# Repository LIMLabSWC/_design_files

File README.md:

# _design_files

This repository stores the design files for all custom-made mechanical and electronic parts used in the lab.  
It is mirrored to the shared folder at:  
`/mnt/ceph/_design_files`

## Quick Start

- **Looking for a specific design?**
  - See the summary table below to find which folder contains the files you need.
  - Each major folder contains a README or index to help you navigate subfolders and file types.
- **Cloning the repository?**
  - Use `git clone --recurse-submodules` to get all submodules (see below for details).
- **Need to open a file?**
  - See folder READMEs for recommended software for each file type (e.g., Autodesk Inventor for `.ipt`, Eagle for `.sch`/`.brd`).

## Repository Structure Summary

| Folder                | Description                              | Main File Types      | Questions? Ask:          |
|-----------------------|------------------------------------------|----------------------|--------------------------|
| rat_behav_rig         | Rat behavioral rig CAD & docs            | .ipt, .stl, .pdf     | Viktor, Dammy, Lillianne |
| mouse-box             | Mouse behavioral box designs             | .ipt, .stl, .pdf     | Dammy, Quentin           |
| Repix_CAD_files       | Neuropixels implant design files         | .step, .stl          | Viktor, Elena            |
| np_calibration_files  | Neuropixels probe calibration data       | .csv                 | Viktor                   |
| Edmunds_designs       | Submodule: Edmund Chong's designs        | .ipt, .stl           | Edmund                   |

## Folder Structure

```
.
├── Edmunds_designs      # Submodule: Edmund Chong's mechanical designs
├── Repix_CAD_files      # Design files for Neuropixels implants     
├── mouse-box            # Design files for the mouse behavioral box
├── np_calibration_files # Neuropixels configuration files
├── rat_behav_rig        # Design files for the rat behavioral rig   
└── README.md
```

## External Design Repositories (Git Submodules)

Some folders in this repository are **Git submodules**—they link to external repositories maintained by individual lab members or collaborators.  
This structure allows each contributor to manage their own designs independently while keeping everything accessible in one place.

### Example: `Edmunds_designs`

- Maintained by: **Edmund Chong**
- Source repo: [edmundchong/Inventor](https://github.com/edmundchong/Inventor)
- Contains: Inventor files for various lab components

## About `.gitmodules`

The `.gitmodules` file tracks all submodules in this repository. It records the path and URL for each submodule, ensuring that everyone who clones the repository can initialize and update submodules easily.  
**Keep this file as long as you use submodules.** If you remove all submodules, you can safely delete `.gitmodules`.

## Cloning This Repository (with Submodules)

### Enabling Auto-Sync for Submodules (Git Hook)

To keep submodules like `Edmunds_designs` automatically in sync after pulling updates, this repository includes a Git hook stored in `.githooks/`.

After cloning, run:

```bash
./setup_hooks.sh
```

This configures Git to use the tracked hook, which:

- Automatically fetches and updates submodules after each `git pull`
- Commits and pushes the updated submodule pointer (if needed)

You only need to run this once per machine.

**Advanced:** You can customize or add your own hooks in the `.githooks/` directory if you want to automate other Git actions.

### Cloning with Submodules

To ensure you clone all linked submodules:

```bash
git clone --recurse-submodules https://github.com/akramilab/_design_files.git
```

If you've already cloned the repo without submodules:

```bash
git submodule update --init --recursive
```

### Keeping Submodules Up to Date Manually

To manually update a submodule (e.g., Edmund's):

```bash
cd Edmunds_designs
git pull origin main  # or the appropriate branch
cd ..
git add Edmunds_designs
git commit -m "Update Edmunds_designs submodule"
git push
```

Repeat for other submodules as needed.

### Notes

- Only maintainers of a submodule's source repo should make edits inside those folders.
- To contribute to a submodule, fork it or contact its maintainer.
- To **add a new submodule**, please contact the main repository maintainer.

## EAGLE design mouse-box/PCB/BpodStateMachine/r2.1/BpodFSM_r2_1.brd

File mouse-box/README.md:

# mouse-box

**Purpose:**
Design files for the mouse behavioral box, including mechanical parts, enclosures, PCBs, and accessories.

## Subfolders & Files

- `SP_box/` — CAD files for the single poke (SP) mouse box
- `PCB/` — Printed circuit board designs (modules, obsolete versions, etc.)
- `Nose Port/` — Nose port mechanical files
- `Head_fixation/` — Head fixation device designs (final and older versions)
- `Enclosure/` — Main enclosure CAD files
- `OldVersions/` — Archived/older versions of parts
- `Walls_schem.idw`, `Walls_schem.pdf` — Wall schematics (Inventor drawing and PDF)
- `Thumbs.db` — Windows thumbnail cache (can be ignored)

## File Types & Recommended Software

- `.ipt`, `.idw` — Autodesk Inventor (2021+ recommended)
- `.stl`, `.step`, `.stp` — 3D models (Inventor, Fusion 360, or free viewers)
- `.pdf` — Drawings, schematics, or documentation (any PDF reader)
- `.dxf`, `.dwg` — 2D CAD (AutoCAD, LibreCAD, or compatible)
- `.sch`, `.brd`, `.zip` (PCB) — Eagle or KiCad (for PCB design)
- `.db` — Windows system file (not needed for design work)

## How to Use

- Open CAD files with the recommended software above.
- See subfolder READMEs (if present) for part-specific instructions or assembly notes.
- For PCB work, see the `PCB/` folder and its submodules for details.
- For fabrication, check for `.pdf` or `.dxf` files for laser cutting or machining.

## Maintainer

- TBD (add name/email here)

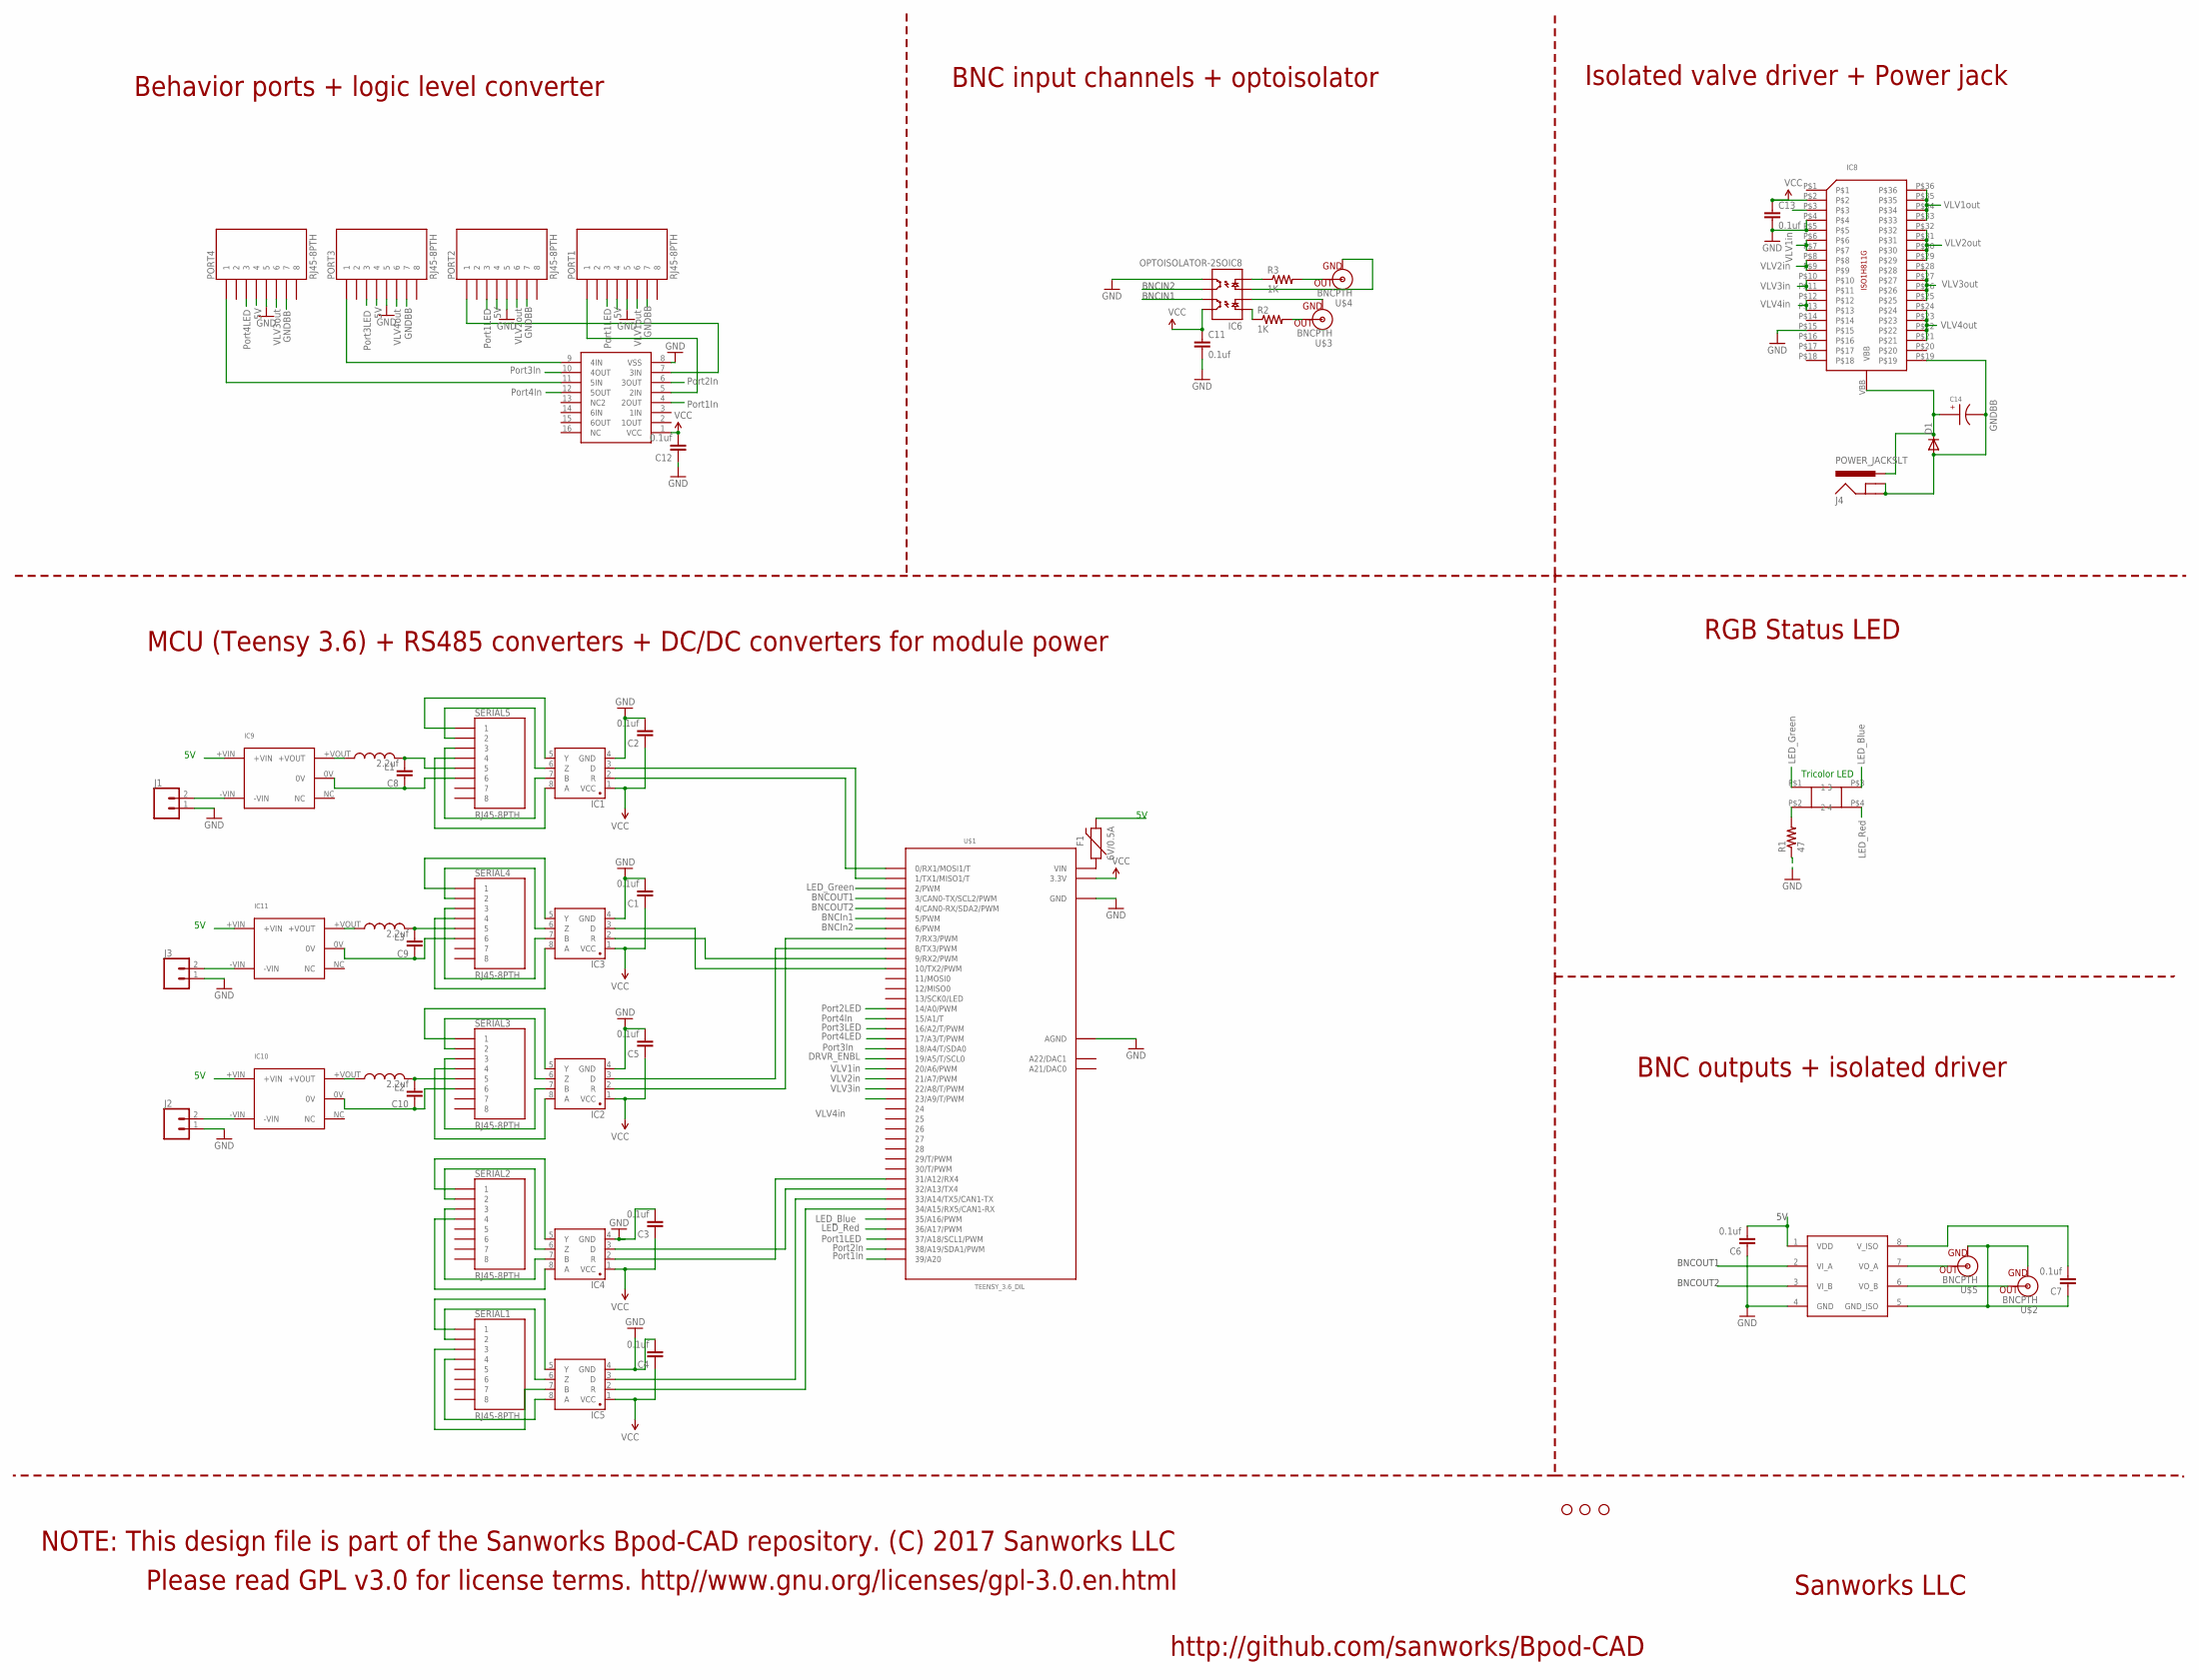
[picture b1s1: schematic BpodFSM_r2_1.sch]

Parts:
C1, C2, C3, C4, C5, C6, C7, C11, C12, C13: 0.1uf; 1206
C8, C9, C10: 2.2uf; 1206
C14: EEE-FK1H100UR
D1: DIODE-DO214AA; DO214AA
F1: 6V/0.5A; 1206
IC1, IC2, IC3, IC4, IC5: SN65HVD31DR; SO08
IC6: OPTOISOLATOR-2SOIC8; SO08-2
IC7: ADUM5240; SO08
IC8: ISO1H811G
IC9, IC10, IC11: MTU1D0505MC
IC12: CD4050; SO16
J1, J2, J3: CONN_02; 1X02
J4: POWER_JACKSLT; POWER_JACK_SLOT
JP3, JP4, JP5: STAND-OFF
L1, L2, L3: L-USL3225M; L3225M
PORT1, PORT2, PORT3, PORT4: RJ45-8PTH; RJ45-8
R1: 47; 1206
R2, R3: 1K; 1206
SERIAL1, SERIAL2, SERIAL3, SERIAL4, SERIAL5: RJ45-8PTH; RJ45-8
U$1: TEENSY_3.6_DIL
U$2, U$3, U$4, U$5: BNCPTH; BNC
U$8: SQUARE_TRICOLOR_LED

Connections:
5V: C6.2, F1.2, IC7.1 (VDD), IC9.+VIN, IC10.+VIN, IC11.+VIN, PORT1.4, PORT2.4, PORT3.4, PORT4.4
BNCIN1: IC6.7 (EM1), U$1.6 (6/PWM)
BNCIN2: IC6.6 (CL2), U$1.5 (5/PWM)
BNCOUT1: IC7.3 (VI_B), U$1.4 (4/CAN0-RX/SDA2/PWM)
BNCOUT2: IC7.2 (VI_A), U$1.3 (3/CAN0-TX/SCL2/PWM)
DRVR_ENBL: IC8.P$3, U$1.19/A5 (19/A5/T/SCL0)
GND: C1.2, C2.2, C3.2, C4.2, C5.2, C6.1, C11.2, C12.1, C13.2, IC1.4 (GND), IC2.4 (GND), IC3.4 (GND), IC4.4 (GND), IC5.4 (GND), IC6.5 (EM2), IC7.4 (GND), IC8.P$4, IC8.P$5, IC8.P$15, IC12.8 (VSS), J1.1, J2.1, J3.1, PORT1.5, PORT2.5, PORT3.5, PORT4.5, R1.1, U$1.AGND, U$1.GND, U$1.GND1 (GND)
GNDBB: C14.CATHODE, D1.A, IC8.P$19, J4.GND@1 (GNDBREAK), J4.GND@2 (GND), PORT1.7, PORT2.7, PORT3.7, PORT4.7
ISOGND: C7.1, IC7.5 (GND_ISO), U$2.GND, U$5.GND
LED_BLUE: U$1.35/A16 (35/A16/PWM), U$8.P$3 (3)
LED_GREEN: U$1.2 (2/PWM), U$8.P$1 (1)
LED_RED: U$1.36/A17 (36/A17/PWM), U$8.P$4 (4)
unnamed: IC3.8 (A), SERIAL4.4
unnamed: IC3.7 (B), SERIAL4.3
unnamed: IC3.6 (Z), SERIAL4.2
unnamed: IC3.5 (Y), SERIAL4.1
unnamed: IC3.2 (R), U$1.9 (9/RX2/PWM)
unnamed: IC3.3 (D), U$1.10 (10/TX2/PWM)
unnamed: IC1.8 (A), SERIAL5.4
unnamed: IC1.7 (B), SERIAL5.3
unnamed: IC1.6 (Z), SERIAL5.2
unnamed: IC1.5 (Y), SERIAL5.1
unnamed: IC1.2 (R), U$1.0 (0/RX1/MOSI1/T)
unnamed: IC1.3 (D), U$1.1 (1/TX1/MISO1/T)
unnamed: IC6.3 (A2), U$4.GND
unnamed: R3.2, U$4.S (OUT)
unnamed: R2.2, U$3.S (OUT)
unnamed: IC6.2 (C1), U$3.GND
unnamed: IC2.8 (A), SERIAL3.4
unnamed: IC2.7 (B), SERIAL3.3
unnamed: IC2.6 (Z), SERIAL3.2
unnamed: IC12.7 (3IN), PORT2.1
unnamed: IC2.5 (Y), SERIAL3.1
unnamed: IC2.2 (R), U$1.7 (7/RX3/PWM)
unnamed: C8.2, L1.2, SERIAL5.5
unnamed: IC12.9 (4IN), PORT3.1
unnamed: R1.2, U$8.P$2 (2)
unnamed: C8.1, IC9.0V, SERIAL5.6
unnamed: IC7.7 (VO_A), U$5.S (OUT)
unnamed: IC2.3 (D), U$1.8 (8/TX3/PWM)
unnamed: F1.1, U$1.VIN
unnamed: IC7.6 (VO_B), U$2.S (OUT)
unnamed: IC12.11 (5IN), PORT4.1
unnamed: IC5.8 (A), SERIAL1.4
unnamed: IC5.7 (B), SERIAL1.3
unnamed: IC5.6 (Z), SERIAL1.2
unnamed: IC5.5 (Y), SERIAL1.1
unnamed: IC4.8 (A), SERIAL2.4
unnamed: IC4.7 (B), SERIAL2.3
unnamed: IC4.6 (Z), SERIAL2.2
unnamed: IC9.+VOUT, L1.1
unnamed: IC4.5 (Y), SERIAL2.1
unnamed: IC9.-VIN, J1.2
unnamed: IC5.2 (R), U$1.34/A15 (34/A15/RX5/CAN1-RX)
unnamed: C10.1, IC10.0V, SERIAL3.6
unnamed: C10.2, L2.2, SERIAL3.5
unnamed: IC10.+VOUT, L2.1
unnamed: IC10.-VIN, J2.2
unnamed: C9.1, IC11.0V, SERIAL4.6
unnamed: IC5.3 (D), U$1.33/A14 (33/A14/TX5/CAN1-TX)
unnamed: C9.2, L3.2, SERIAL4.5
unnamed: IC11.+VOUT, L3.1
unnamed: IC11.-VIN, J3.2
unnamed: IC4.2 (R), U$1.31/A12 (31/A12/RX4)
unnamed: IC4.3 (D), U$1.32/A13 (32/A13/TX4)
unnamed: IC6.1 (A1), R2.1
unnamed: IC6.4 (C2), R3.1
unnamed: IC12.5 (2IN), PORT1.1
unnamed: C7.2, IC7.8 (V_ISO)
PORT1IN: IC12.4 (2OUT), U$1.39/A20
PORT1LED: PORT1.3, U$1.37/A18 (37/A18/SCL1/PWM)
PORT2IN: IC12.6 (3OUT), U$1.38/A19 (38/A19/SDA1/PWM)
PORT2LED: PORT2.3, U$1.14/A0 (14/A0/PWM)
PORT3IN: IC12.10 (4OUT), U$1.18/A4 (18/A4/T/SDA0)
PORT3LED: PORT3.3, U$1.16/A2 (16/A2/T/PWM)
PORT4IN: IC12.12 (5OUT), U$1.15/A1 (15/A1/T)
PORT4LED: PORT4.3, U$1.17/A3 (17/A3/T/PWM)
VBB: C14.ANODE, D1.C, IC8.VBB, J4.PWR
VCC: C1.1, C2.1, C3.1, C4.1, C5.1, C11.1, C12.2, C13.1, IC1.1 (VCC), IC2.1 (VCC), IC3.1 (VCC), IC4.1 (VCC), IC5.1 (VCC), IC6.8 (CL1), IC8.P$2, IC12.1 (VCC), U$1.3.3V, U$1.3.3V3 (3.3V)
VLV1IN: IC8.P$6, IC8.P$7, U$1.23/A9 (23/A9/T/PWM)
VLV1OUT: IC8.P$33, IC8.P$34, IC8.P$35, IC8.P$36, PORT1.6
VLV2IN: IC8.P$8, IC8.P$9, U$1.22/A8 (22/A8/T/PWM)
VLV2OUT: IC8.P$29, IC8.P$30, IC8.P$31, IC8.P$32, PORT2.6
VLV3IN: IC8.P$12, IC8.P$13, U$1.20/A6 (20/A6/PWM)
VLV3OUT: IC8.P$21, IC8.P$22, IC8.P$23, IC8.P$24, PORT3.6
VLV4IN: IC8.P$10, IC8.P$11, U$1.21/A7 (21/A7/PWM)
VLV4OUT: IC8.P$25, IC8.P$26, IC8.P$27, IC8.P$28, PORT4.6

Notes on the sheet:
Tricolor LED
LED_Blue
LED_Red
LED_Green
BNCIN1
BNCIN2
BNCIn1
BNCIn2
BNCOUT2
BNCOUT1
Port1In
Port2In
Port3In
Port4In
Port1LED
Port2LED
Port3LED
Port4LED
DRVR_ENBL
VLV2in
VLV3in
VLV4in
VLV1in
GNDBB
VLV1out
VLV2out
VLV3out
VLV4out
Sanworks LLC
http://github.com/sanworks/Bpod-CAD
Please read GPL v3.0 for license terms. http//www.gnu.org/licenses/gpl-3.0.en.html
NOTE: This design file is part of the Sanworks Bpod-CAD repository. (C) 2017 Sanworks LLC
Behavior ports + logic level converter
BNC input channels + optoisolator
Isolated valve driver + Power jack
RGB Status LED
BNC outputs + isolated driver
MCU (Teensy 3.6) + RS485 converters + DC/DC converters for module power

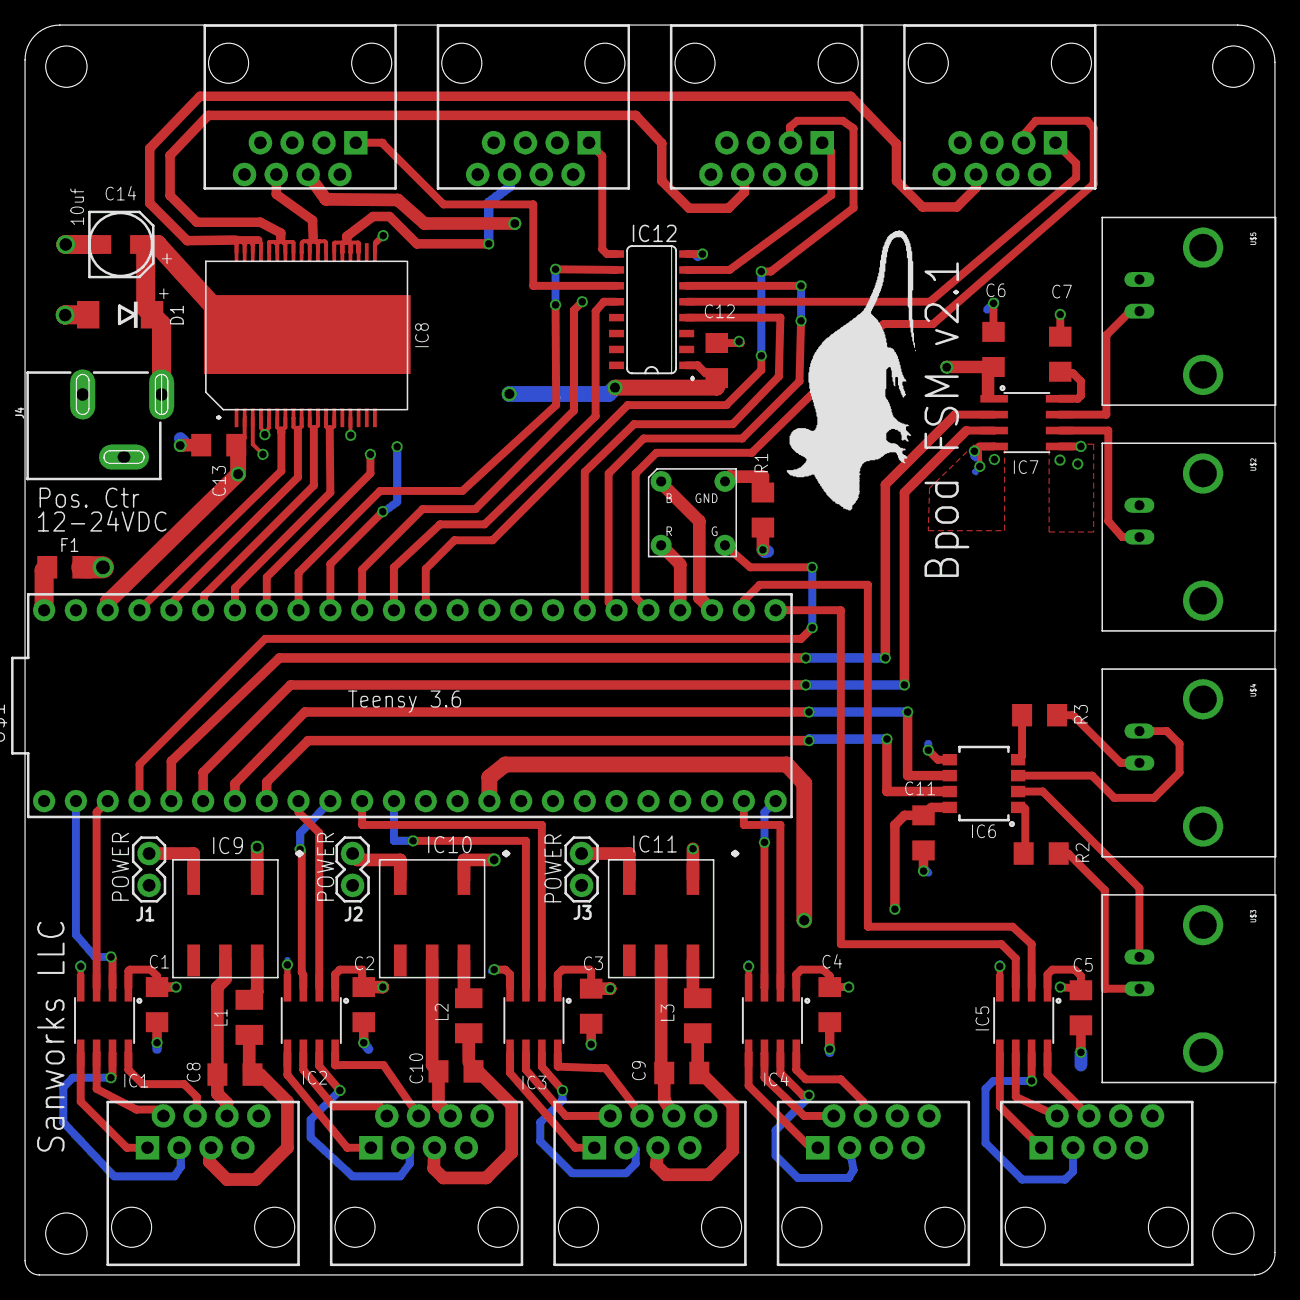
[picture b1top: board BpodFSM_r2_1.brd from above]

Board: 4 copper layers, 99.8 x 99.8 mm, 58 parts (0 on the bottom side), 87 nets.

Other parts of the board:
JP1: STAND-OFF
U$9: MOUSELOGO

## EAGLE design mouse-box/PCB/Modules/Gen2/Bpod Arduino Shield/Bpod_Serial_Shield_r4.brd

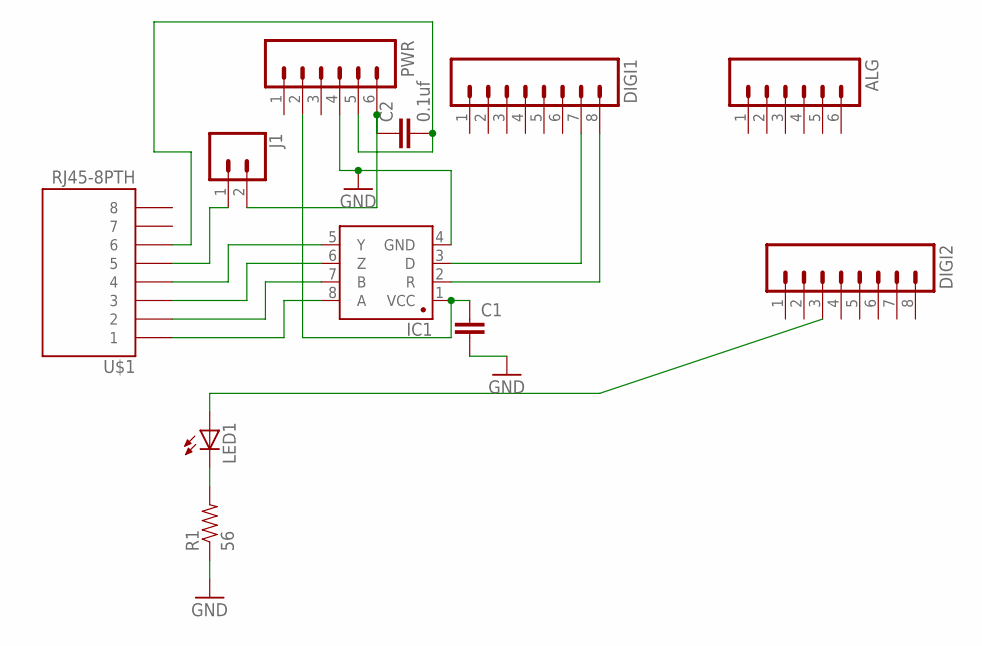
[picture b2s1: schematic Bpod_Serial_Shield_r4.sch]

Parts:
ALG: M06LONGPADS; 1X06_LONGPADS
C1: CAP1206; 1206
C2: 0.1uf; 1206
DIGI1, DIGI2: M08LONGPADS; 1X08_LONGPADS
IC1: SN65HVD31DR; SO08
J1: CONN_02; 1X02
LED1: LEDCHIPLED_1206; CHIPLED_1206
PWR: M06LONGPADS; 1X06_LONGPADS
R1: 56; 1206
U$1: RJ45-8PTH; RJ45-8

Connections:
GND: C1.2, IC1.4 (GND), PWR.4, R1.1
unnamed: C1.1, IC1.1 (VCC), PWR.2
unnamed: LED1.C, R1.2
unnamed: DIGI2.3, LED1.A
unnamed: DIGI1.7, IC1.3 (D)
unnamed: C2.1, J1.2, PWR.6
unnamed: DIGI1.8, IC1.2 (R)
unnamed: IC1.8 (A), U$1.1
unnamed: IC1.7 (B), U$1.2
unnamed: IC1.6 (Z), U$1.3
unnamed: IC1.5 (Y), U$1.4
unnamed: C2.2, PWR.5, U$1.6
unnamed: J1.1, U$1.5

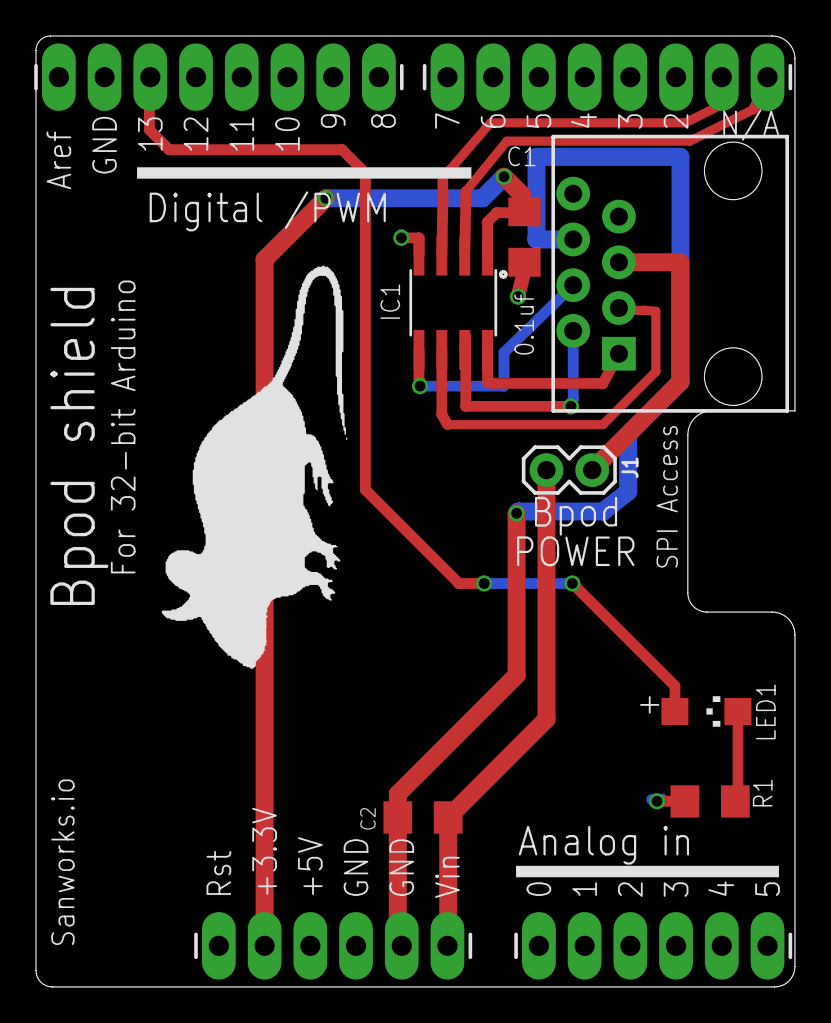
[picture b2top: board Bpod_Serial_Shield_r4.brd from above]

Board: 2 copper layers, 42.2 x 52.8 mm, 12 parts (0 on the bottom side), 13 nets.

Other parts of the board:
U$2: MOUSELOGO

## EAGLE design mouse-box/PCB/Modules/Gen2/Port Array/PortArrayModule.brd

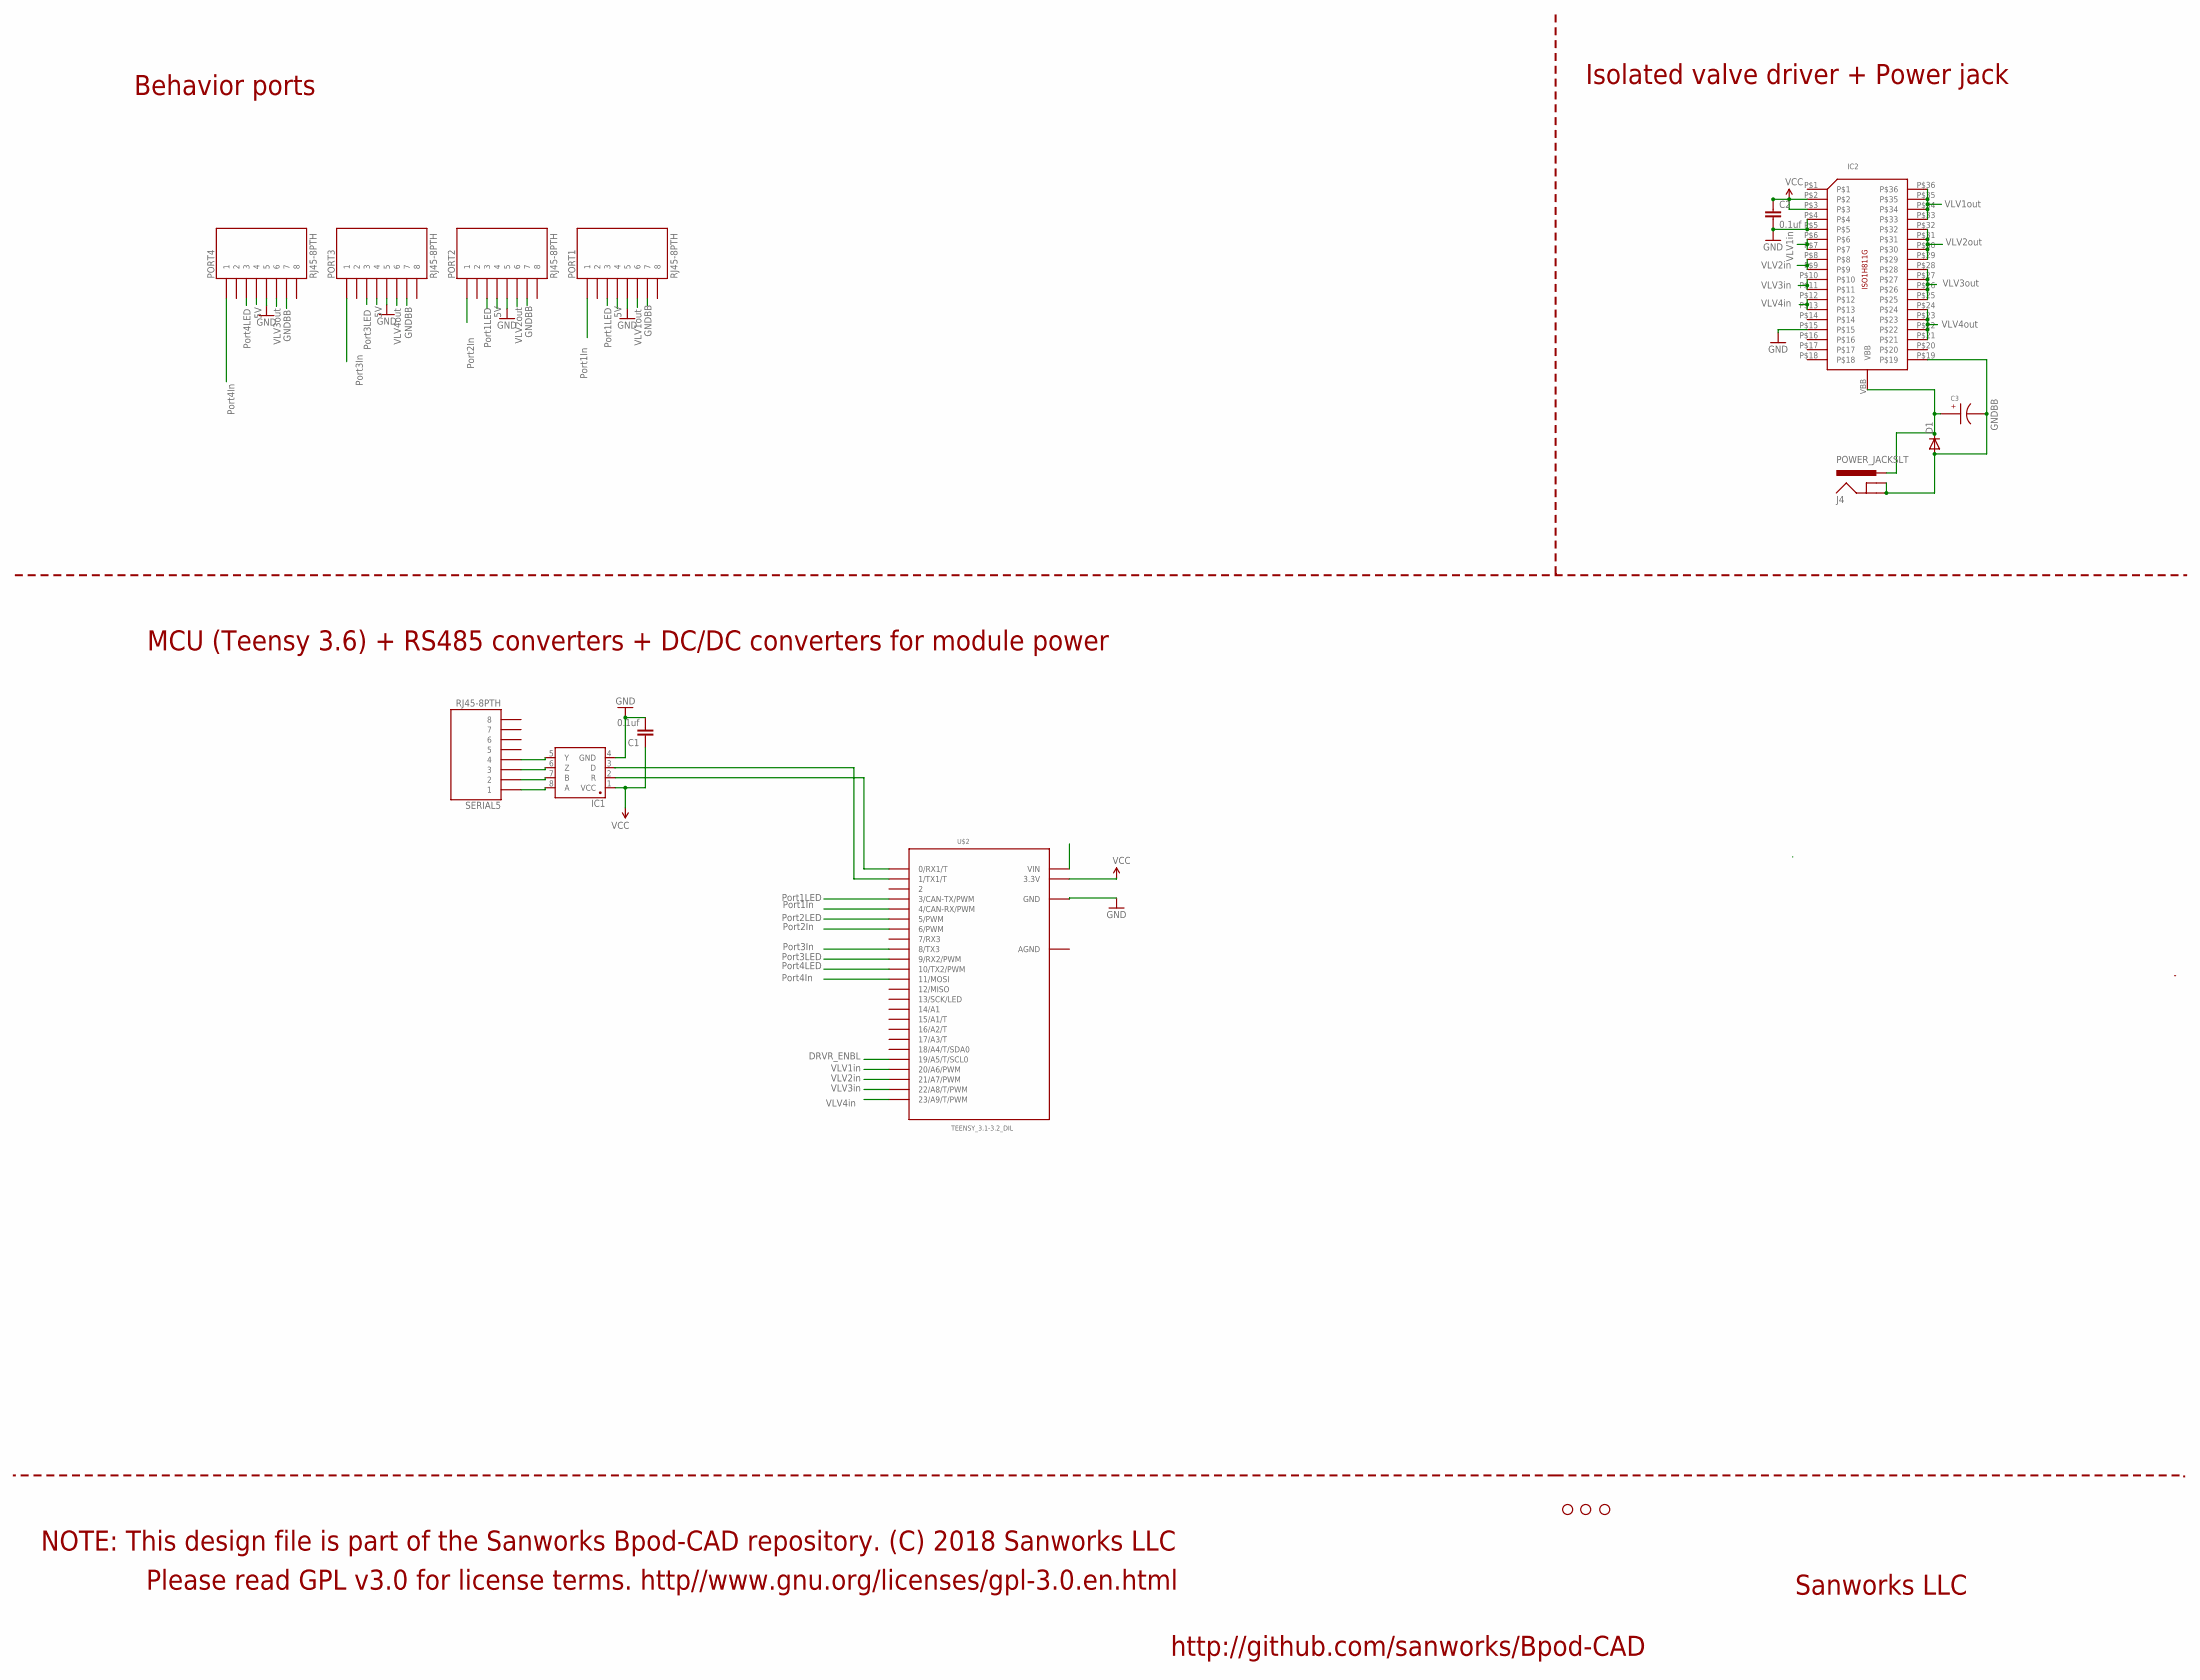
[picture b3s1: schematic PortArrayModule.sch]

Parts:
C1, C2: 0.1uf; 1206@1
C3: EEE-FK1H100UR
D1: DIODE-DO214AA; DO214AA
IC1: SN65HVD31DR; SO08
IC2: ISO1H811G
J4: POWER_JACKSLT; POWER_JACK_SLOT
JP3, JP4, JP5: STAND-OFF
PORT1, PORT2, PORT3, PORT4: RJ45-8PTH; RJ45-8
SERIAL5: RJ45-8PTH; RJ45-8
U$2: TEENSY_3.1-3.2_DIL; TEENSY_3.0-3.2&LC_DIL

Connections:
5V: PORT1.4, PORT2.4, PORT3.4, PORT4.4, U$2.VIN
AGND: U$2.AGND
DRVR_ENBL: U$2.19/A5 (19/A5/T/SCL0)
GND: C1.2, C2.2, IC1.4 (GND), IC2.P$4, IC2.P$5, IC2.P$15, PORT1.5, PORT2.5, PORT3.5, PORT4.5, U$2.GND
GNDBB: C3.CATHODE, D1.A, IC2.P$19, J4.GND@1 (GNDBREAK), J4.GND@2 (GND), PORT1.7, PORT2.7, PORT3.7, PORT4.7
unnamed: IC1.8 (A), SERIAL5.1
unnamed: IC1.7 (B), SERIAL5.2
unnamed: IC1.6 (Z), SERIAL5.3
unnamed: IC1.5 (Y), SERIAL5.4
unnamed: IC1.3 (D), U$2.1 (1/TX1/T)
unnamed: IC1.2 (R), U$2.0 (0/RX1/T)
PORT1IN: PORT1.1, U$2.4 (4/CAN-RX/PWM)
PORT1LED: PORT1.3, U$2.3 (3/CAN-TX/PWM)
PORT2IN: PORT2.1, U$2.6 (6/PWM)
PORT2LED: PORT2.3, U$2.5 (5/PWM)
PORT3IN: PORT3.1, U$2.8 (8/TX3)
PORT3LED: PORT3.3, U$2.9 (9/RX2/PWM)
PORT4IN: PORT4.1, U$2.11 (11/MOSI)
PORT4LED: PORT4.3, U$2.10 (10/TX2/PWM)
VBB: C3.ANODE, D1.C, IC2.VBB, J4.PWR
VCC: C1.1, C2.1, IC1.1 (VCC), IC2.P$2, IC2.P$3, U$2.3.3V
VLV1IN: IC2.P$6, IC2.P$7, U$2.20/A6 (20/A6/PWM)
VLV1OUT: IC2.P$33, IC2.P$34, IC2.P$35, IC2.P$36, PORT1.6
VLV2IN: IC2.P$8, IC2.P$9, U$2.21/A7 (21/A7/PWM)
VLV2OUT: IC2.P$29, IC2.P$30, IC2.P$31, IC2.P$32, PORT2.6
VLV3IN: IC2.P$12, IC2.P$13, U$2.23/A9 (23/A9/T/PWM)
VLV3OUT: IC2.P$21, IC2.P$22, IC2.P$23, IC2.P$24, PORT3.6
VLV4IN: IC2.P$10, IC2.P$11, U$2.22/A8 (22/A8/T/PWM)
VLV4OUT: IC2.P$25, IC2.P$26, IC2.P$27, IC2.P$28, PORT4.6

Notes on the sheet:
Port1In
Port2In
Port3In
Port4In
Port1LED
Port2LED
Port3LED
Port4LED
DRVR_ENBL
VLV2in
VLV3in
VLV4in
VLV1in
GNDBB
VLV1out
VLV2out
VLV3out
VLV4out
Sanworks LLC
http://github.com/sanworks/Bpod-CAD
Please read GPL v3.0 for license terms. http//www.gnu.org/licenses/gpl-3.0.en.html
NOTE: This design file is part of the Sanworks Bpod-CAD repository. (C) 2018 Sanworks LLC
Behavior ports
Isolated valve driver + Power jack
MCU (Teensy 3.6) + RS485 converters + DC/DC converters for module power

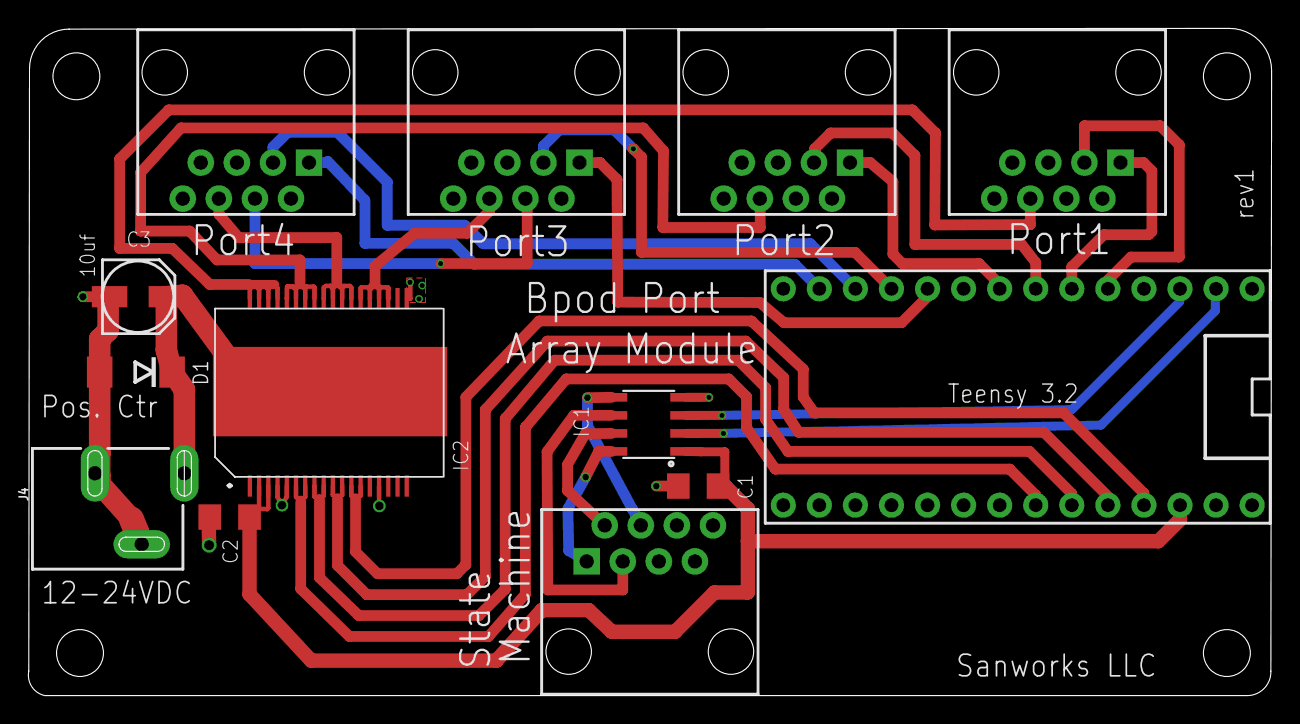
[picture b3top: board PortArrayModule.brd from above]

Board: 4 copper layers, 87.6 x 47.0 mm, 17 parts (0 on the bottom side), 27 nets.

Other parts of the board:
JP1: STAND-OFF

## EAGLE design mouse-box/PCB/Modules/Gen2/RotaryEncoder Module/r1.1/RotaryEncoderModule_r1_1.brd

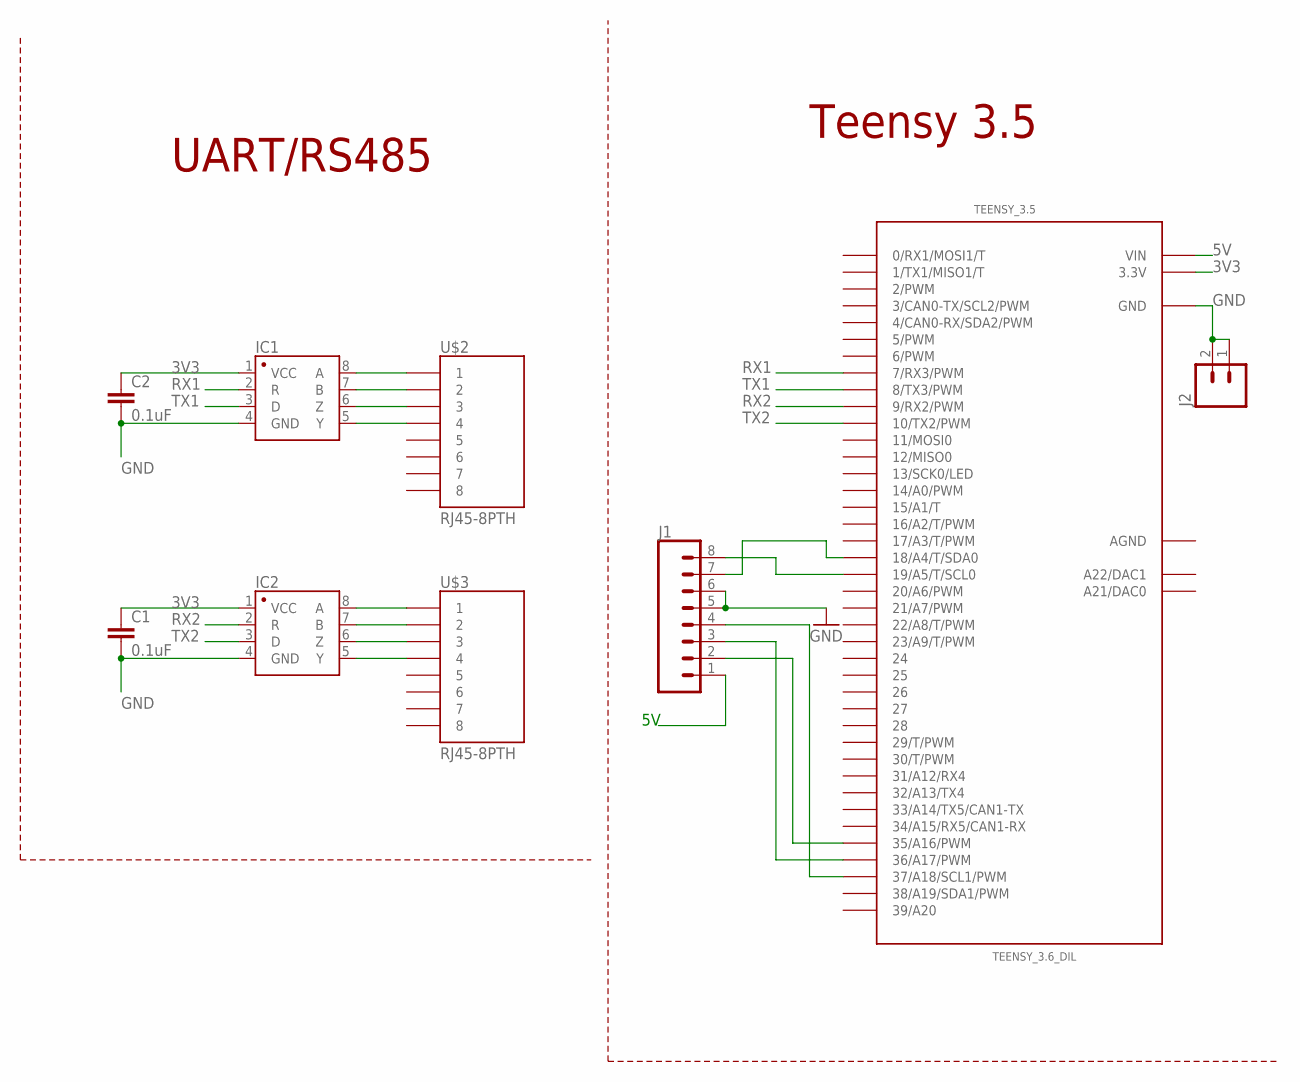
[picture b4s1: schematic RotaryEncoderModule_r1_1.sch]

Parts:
C1, C2: 0.1uF; 1206
IC1, IC2: SN65HVD31DR; SO08
J1: CONN_083.5MM-8; SCREWTERMINAL-3.5MM-8
J2: M023.5MM; SCREWTERMINAL-3.5MM-2
TEENSY_3.5: TEENSY_3.6_DIL
U$2, U$3: RJ45-8PTH; RJ45-8

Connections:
3V3: C1.1, C2.1, IC1.1 (VCC), IC2.1 (VCC), TEENSY_3.5.3.3V, TEENSY_3.5.3.3V3 (3.3V)
5V: J1.1, TEENSY_3.5.VIN
AGND: TEENSY_3.5.AGND
GND: C1.2, C2.2, IC1.4 (GND), IC2.4 (GND), J1.5, J1.6, J2.1, J2.2, TEENSY_3.5.GND, TEENSY_3.5.GND1 (GND)
unnamed: IC1.6 (Z), U$2.3
unnamed: IC1.8 (A), U$2.1
unnamed: IC1.5 (Y), U$2.4
unnamed: IC1.7 (B), U$2.2
unnamed: IC2.6 (Z), U$3.3
unnamed: IC2.5 (Y), U$3.4
unnamed: IC2.8 (A), U$3.1
unnamed: IC2.7 (B), U$3.2
unnamed: J1.8, TEENSY_3.5.19/A5 (19/A5/T/SCL0)
unnamed: J1.7, TEENSY_3.5.18/A4 (18/A4/T/SDA0)
unnamed: J1.2, TEENSY_3.5.35/A16 (35/A16/PWM)
unnamed: J1.3, TEENSY_3.5.36/A17 (36/A17/PWM)
unnamed: J1.4, TEENSY_3.5.37/A18 (37/A18/SCL1/PWM)
RX1: IC1.2 (R), TEENSY_3.5.7 (7/RX3/PWM)
RX2: IC2.2 (R), TEENSY_3.5.9 (9/RX2/PWM)
TX1: IC1.3 (D), TEENSY_3.5.8 (8/TX3/PWM)
TX2: IC2.3 (D), TEENSY_3.5.10 (10/TX2/PWM)

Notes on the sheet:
Teensy 3.5
UART/RS485

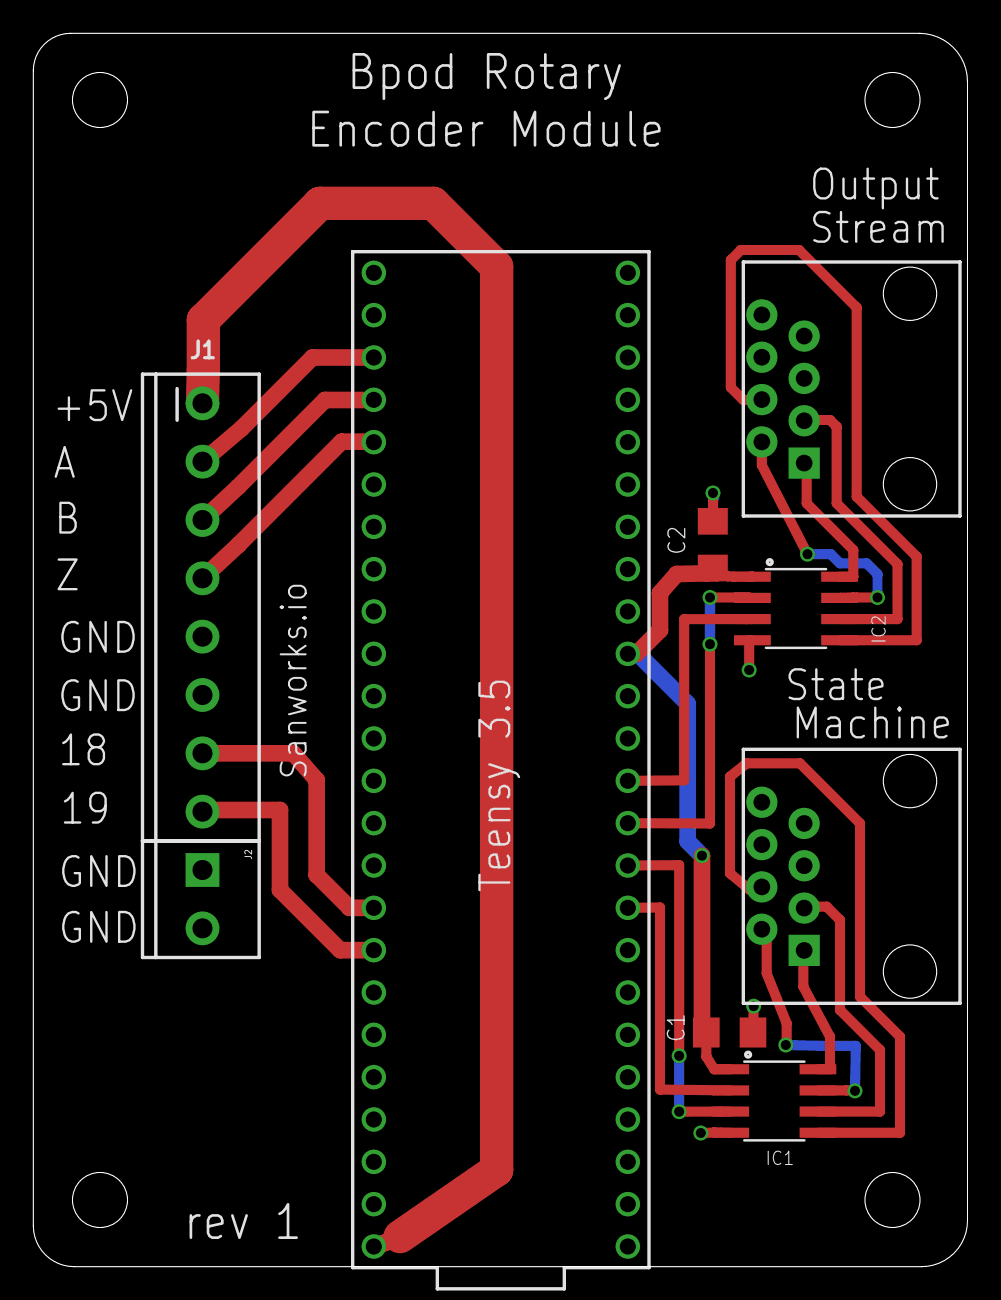
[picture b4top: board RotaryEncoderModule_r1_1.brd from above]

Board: 2 copper layers, 56.0 x 74.0 mm, 13 parts (0 on the bottom side), 20 nets.

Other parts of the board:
U$5, U$6, U$7, U$8: STAND-OFF

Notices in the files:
parts and their libraries:
SparkFun-Passives: Licensing: CC v3.0 Share-Alike You are welcome to use this library for commercial purposes.
SparkFun-DiscreteSemi: Licensing: Creative Commons ShareAlike 4.0 International - https://creativecommons.org/licenses/by-sa/4.0
